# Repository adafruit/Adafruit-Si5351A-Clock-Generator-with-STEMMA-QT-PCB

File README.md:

## Adafruit Adafruit Si5351A Clock Generator with STEMMA QT 8KHz to 160MHz PCB

<a href="http://www.adafruit.com/products/5640"><br/>
Click here to purchase one from the Adafruit shop</a>

PCB files for the Adafruit Adafruit Si5351A Clock Generator with STEMMA QT 8KHz to 160MHz. 

Format is EagleCAD schematic and board layout
* https://www.adafruit.com/product/5640

### Description

Never hunt around for another crystal again, with the Si5351A clock generator breakout from Adafruit! This chip has a precision 25MHz crystal reference and internal PLL and dividers so it can generate just about any frequency, from <8KHz up to 150+ MHz.

The Si5351A clock generator is an I2C controller clock generator. It uses the onboard precision clock to drive multiple PLL's and clock dividers using I2C instructions. By setting up the PLL and dividers you can create precise and arbitrary frequencies. There are three independent outputs, and each one can have a different frequency. Outputs are 3Vpp, either through a breadboard-friendly header or, for RF work, an optional edge-launch SMA connector for output #1. (If you need SMA-connector outputs for all three ports, check out the non-QT breakout here)

To get you going fast, we spun up a custom-made PCB in the STEMMA QT form factor, making it easy to interface with. The STEMMA QT connectors on either side are compatible with the SparkFun Qwiic I2C connectors. This allows you to make solderless connections between your development board and the Si5351 or to chain it with a wide range of other sensors and accessories using a compatible cable. Onboard 3.3V LDO and level shifters means its ready for use with 3V or 5V power and logic!

Best of all, we even have a great tutorial and library to get you started! Our code is designed for use with the Arduino-compatible microcontrollers and CircuitPython/Python using I2C support.

### License

Adafruit invests time and resources providing this open source design, please support Adafruit and open-source hardware by purchasing products from [Adafruit](https://www.adafruit.com)!

Designed by Limor Fried/Ladyada for Adafruit Industries.

Creative Commons Attribution/Share-Alike, all text above must be included in any redistribution. 
See license.txt for additional details.

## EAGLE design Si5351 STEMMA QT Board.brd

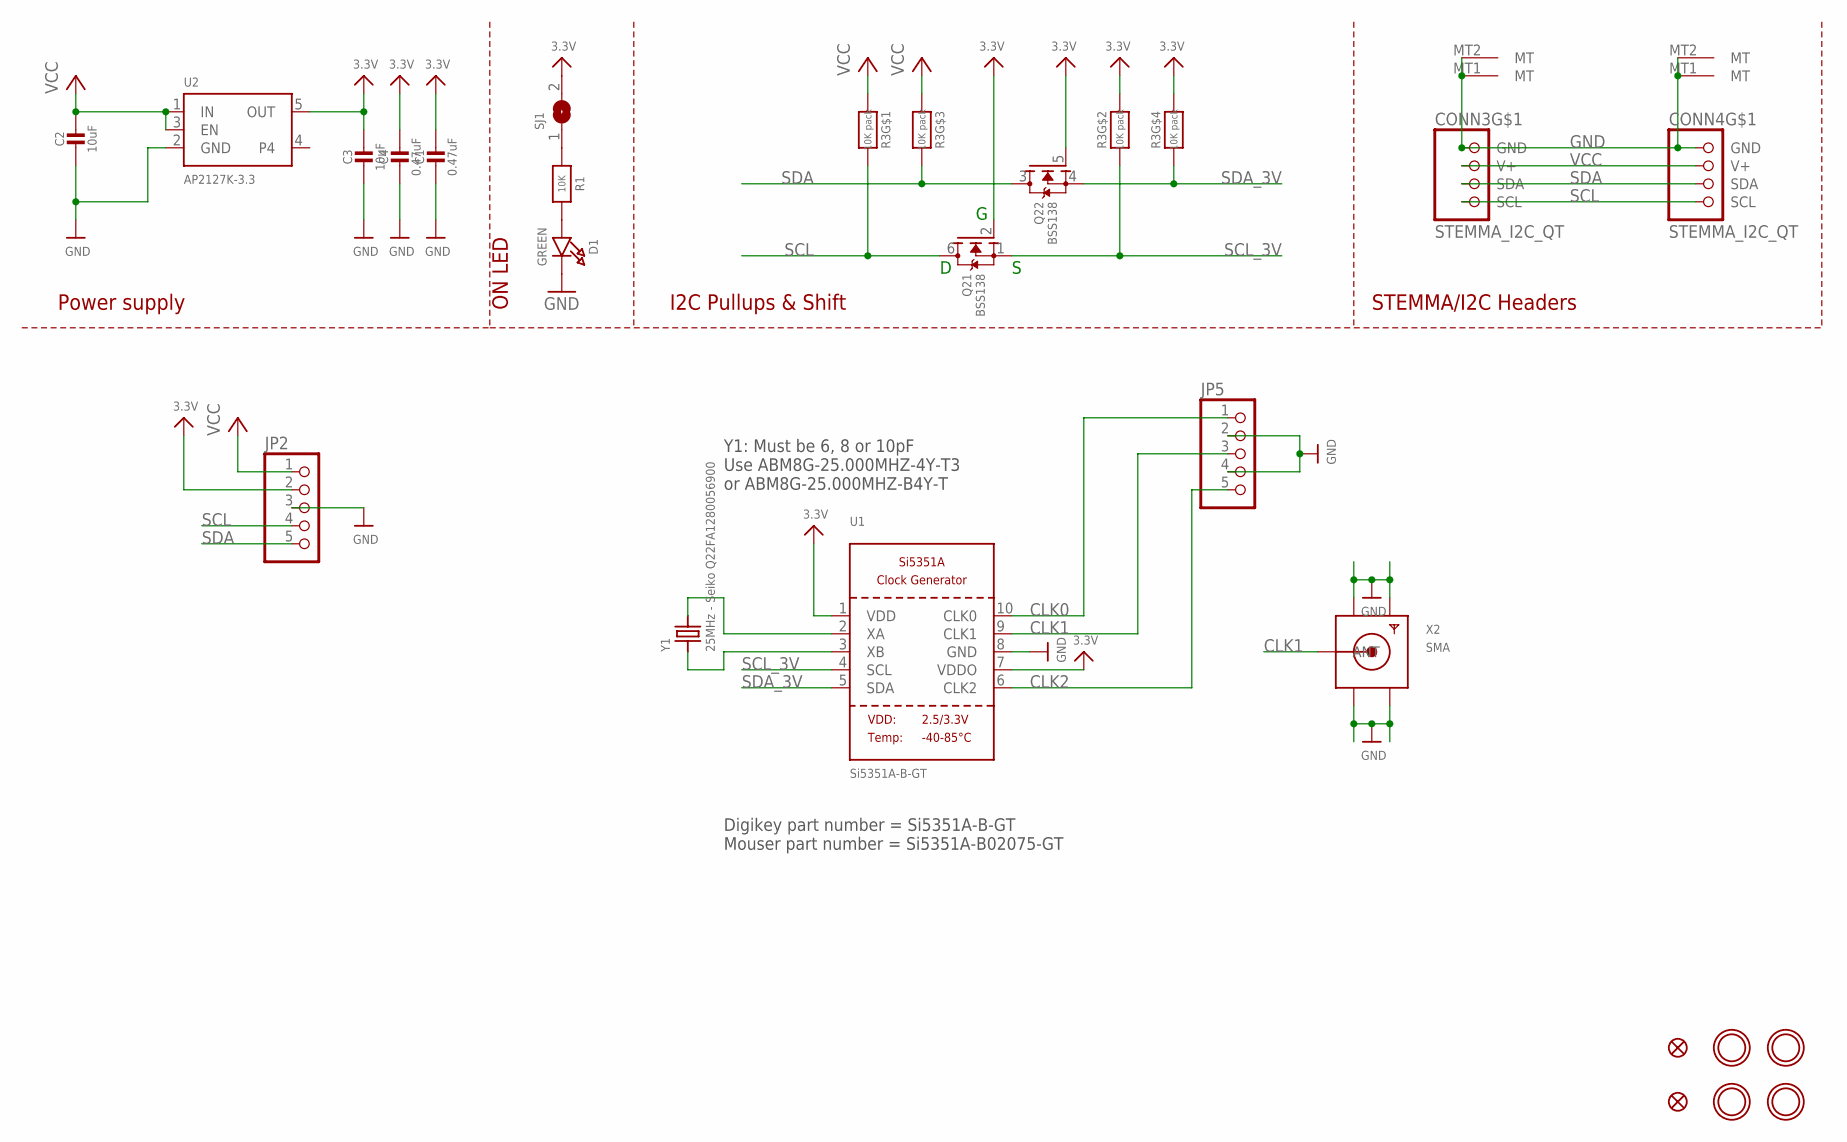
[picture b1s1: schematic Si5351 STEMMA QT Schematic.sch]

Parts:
C1, C4: 0.47uF; 0603-NO
C2, C3: 10uF; 0805-NO
CONN3, CONN4: STEMMA_I2C_QT; JST_SH4
D1: GREEN; CHIPLED_0603_NOOUTLINE
FID3, FID4: FIDUCIAL_1MM
JP2, JP5: HEADER-1X570MIL; 1X05_ROUND_70
Q2: BSS138; SOT363
R1: 10K; 0603-NO
R3: 10K pack; RESPACK_4X0603
SJ1: SOLDERJUMPERCLOSED; SOLDERJUMPER_CLOSEDWIRE
U1: Si5351A-B-GT; MSOP10
U2: AP2127K-3.3; SOT23-5
U$1, U$17, U$19, U$21: MOUNTINGHOLE2.5; MOUNTINGHOLE_2.5_PLATED
X2: SMA; SMA_EDGELAUNCH
Y1: 25MHz - Seiko Q22FA1280056900; CRYSTAL_2X1.6

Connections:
3.3V: C1.1, C3.1, C4.1, JP2.2, Q2.2 (G), Q2.5 (G), R3.2 (1), R3.4 (1), SJ1.2, U1.1 (VDD), U1.7 (VDDO), U2.5 (OUT)
CLK0: JP5.1, U1.10 (CLK0)
CLK1: JP5.3, U1.9 (CLK1), X2.P (ANT)
CLK2: JP5.5, U1.6 (CLK2)
GND: C1.2, C2.2, C3.2, C4.2, CONN3.1 (GND), CONN3.MT1 (MT), CONN3.MT2 (MT), CONN4.1 (GND), CONN4.MT1 (MT), CONN4.MT2 (MT), D1.C, JP2.3, JP5.2, JP5.4, U1.8 (GND), U2.2 (GND), X2.GND@1 (GND4), X2.GND@2 (GND3), X2.GND@3 (GND2), X2.GND@4 (GND1)
unnamed: D1.A, R1.2
unnamed: R1.1, SJ1.1
unnamed: U1.3 (XB), Y1.1
unnamed: U1.2 (XA), Y1.3 (2)
SCL: CONN3.4 (SCL), CONN4.4 (SCL), JP2.4, Q2.6 (D), R3.8 (2)
SCL_3V: Q2.1 (S), R3.7 (2), U1.4 (SCL)
SDA: CONN3.3 (SDA), CONN4.3 (SDA), JP2.5, Q2.3 (D), R3.6 (2)
SDA_3V: Q2.4 (S), R3.5 (2), U1.5 (SDA)
VCC: C2.1, CONN3.2 (V+), CONN4.2 (V+), JP2.1, R3.1, R3.3 (1), U2.1 (IN), U2.3 (EN)

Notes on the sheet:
I2C Pullups & Shift
STEMMA/I2C Headers
ON LED
Power supply
Digikey part number = Si5351A-B-GT Mouser part number = Si5351A-B02075-GT
Y1: Must be 6, 8 or 10pF Use ABM8G-25.000MHZ-4Y-T3 or ABM8G-25.000MHZ-B4Y-T

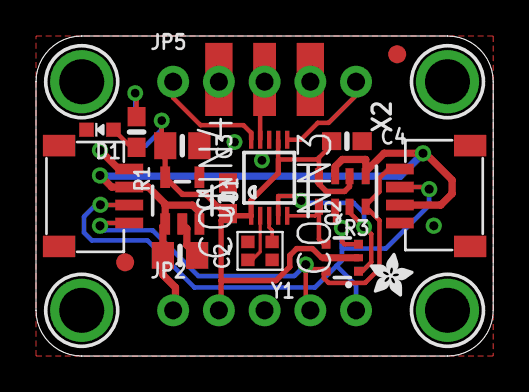
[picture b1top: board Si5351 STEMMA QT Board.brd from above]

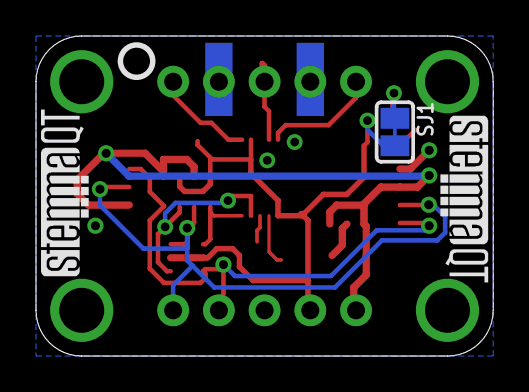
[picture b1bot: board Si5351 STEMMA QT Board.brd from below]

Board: 2 copper layers, 25.4 x 17.8 mm, 46 parts (13 on the bottom side), 14 nets.

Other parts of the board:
PLABEL0: PLABEL0
PLABEL1: PLABEL1
PLABEL2: PLABEL2
PLABEL3: PLABEL3
PLABEL4: PLABEL4
PLABEL5: PLABEL5
PLABEL6: PLABEL6
PLABEL7: PLABEL7
PLABEL8: PLABEL8
PLABEL9: PLABEL9
PLABEL10: PLABEL10
PLABEL11: PLABEL11
PLABEL12: PLABEL12
PLABEL13: PLABEL13
PLABEL14: PLABEL14
PLABEL15: PLABEL15
PLABEL16: PLABEL16
PLABEL17: PLABEL17
PLABEL18: PLABEL18
U$9: ADAFRUIT_2.5MM
U$25: PCBFEAT-REV-040
U$30, U$31: STEMMAQT

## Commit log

2022-11-04 adding cookiecutter output
2022-11-04 adding product copy

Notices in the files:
parts and their libraries:
microbuilder: This work is placed in the public domain, and may be freely used for commercial and non-commercial work with the following conditions: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
